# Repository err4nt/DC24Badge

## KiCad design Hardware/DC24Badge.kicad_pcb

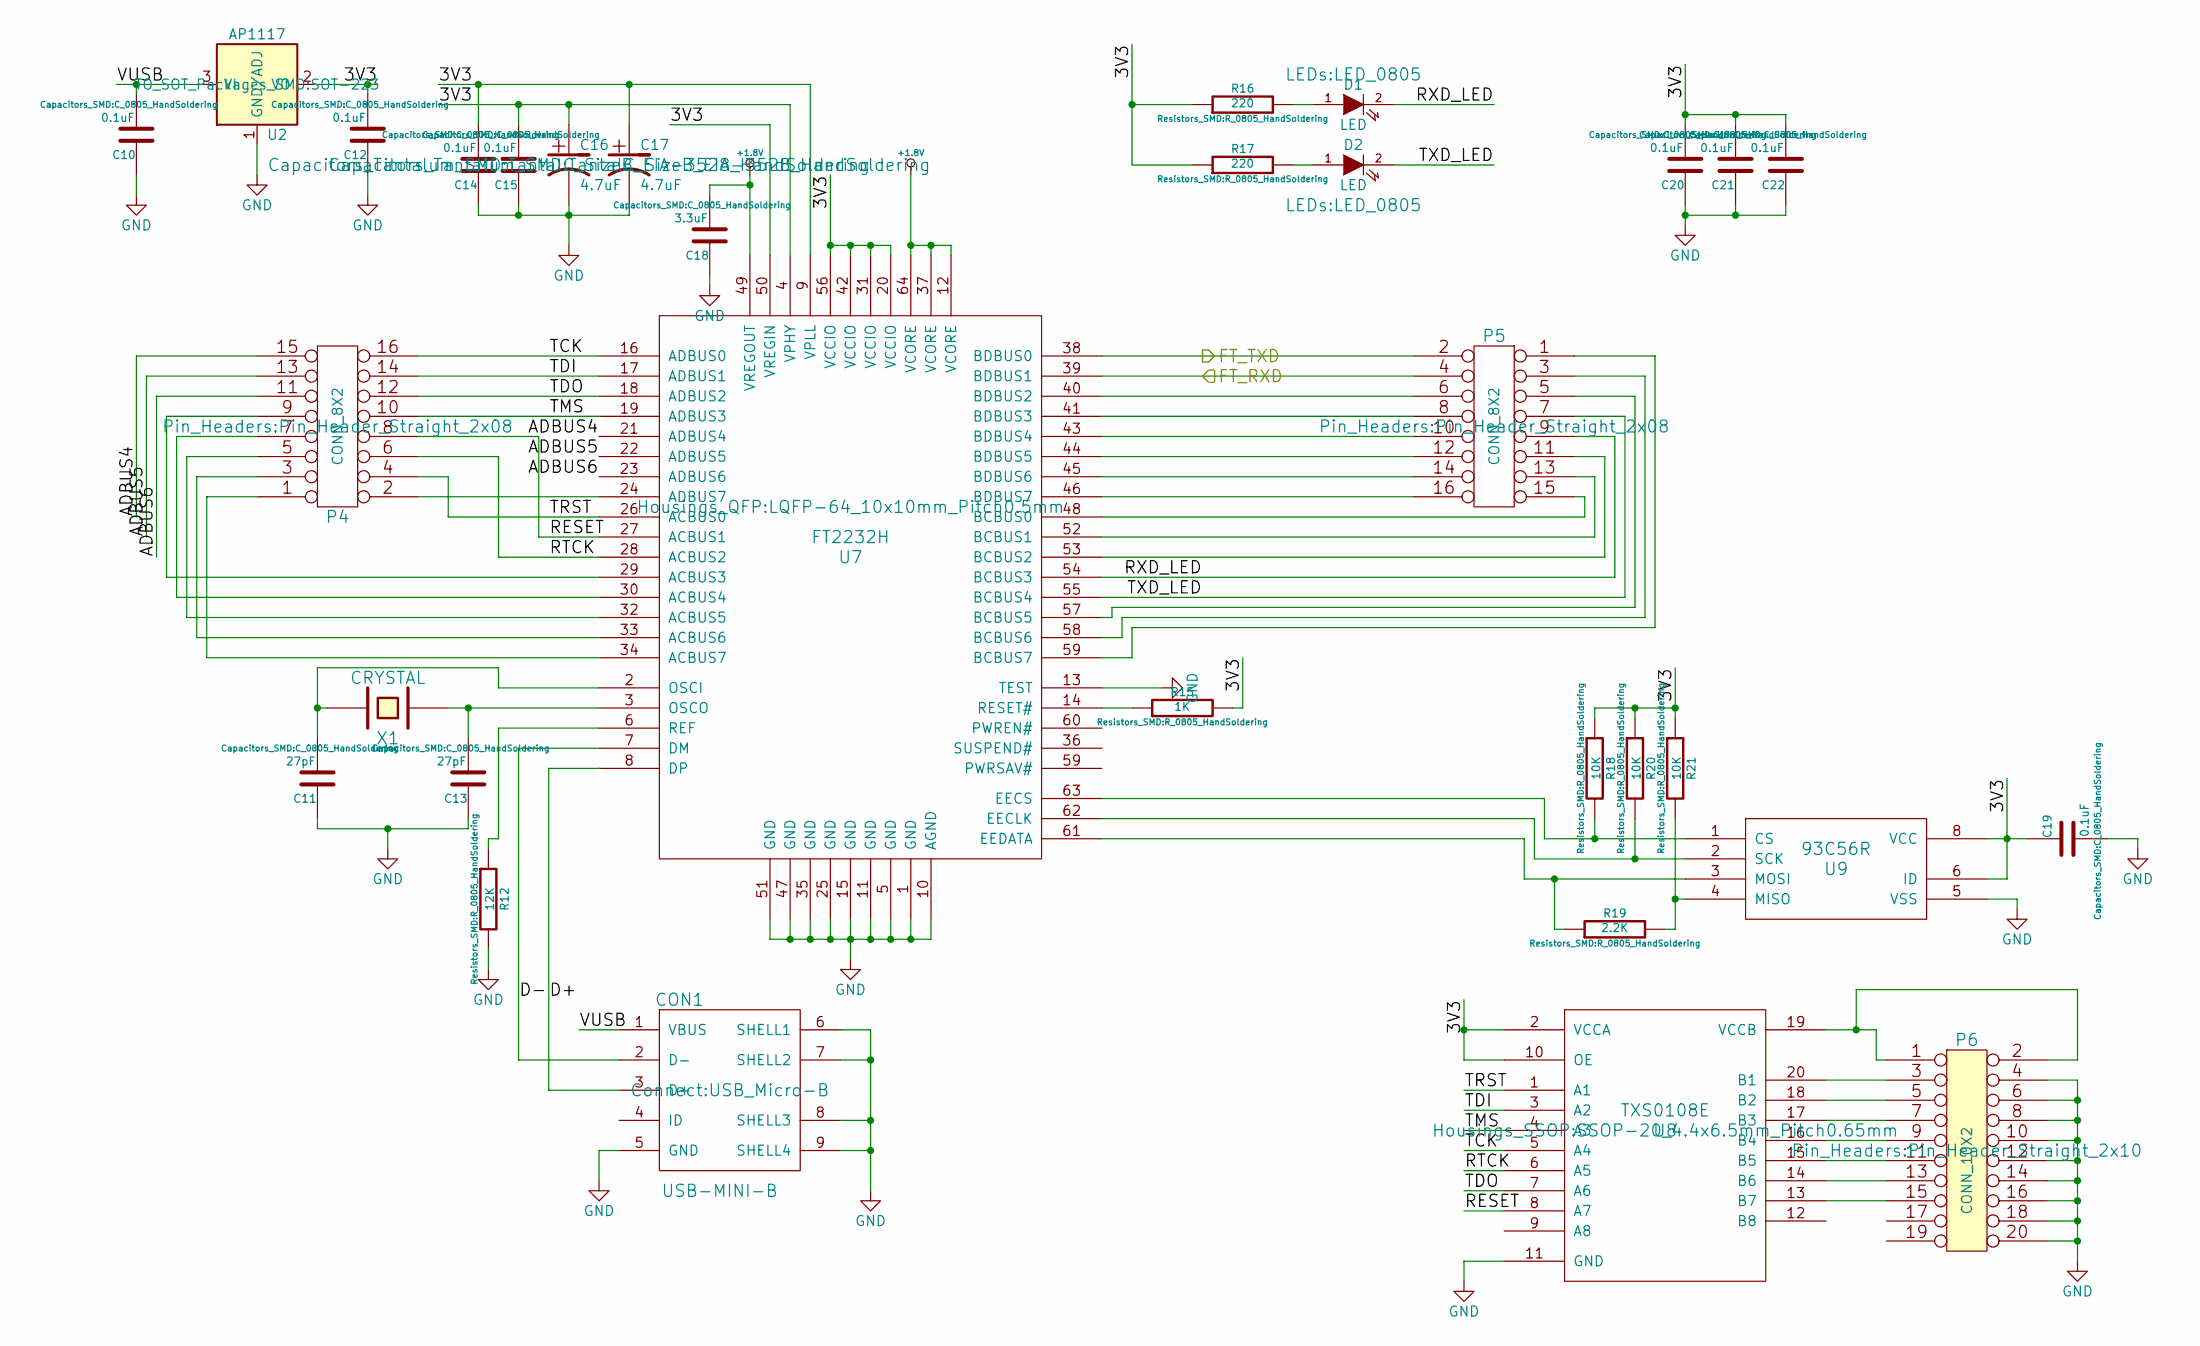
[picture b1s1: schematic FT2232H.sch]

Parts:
C10, C12, C14, C15, C19, C20, C21, C22: 0.1uF; C_0805_HandSoldering; MouserPN 710-885012207072
C11, C13: 27pF; C_0805_HandSoldering; MouserPN 80-C0805C270J5G
C16, C17: 4.7uF; TantalC_SizeB_EIA-3528_HandSoldering; MouserPN 647-F931E475MBA
C18: 3.3uF; C_0805_HandSoldering; MouserPN 77-VJ0805V335ZXQTBC
CON1: USB-MINI-B; USB_Micro-B; MouserPN 798-ZX62D-B-5PA830
D1: LED; LED_0805; MouserPN 720-LGR971-KN-1
D2: LED; LED_0805; MouserPN 720-LHR974-LP-1
P4, P5: CONN_8X2; Pin_Header_Straight_2x08
P6: CONN_10X2; Pin_Header_Straight_2x10; MouserPN 653-XG4C-2031
R12: 12K; R_0805_HandSoldering; MouserPN 667-ERJ-6GEYJ123V
R15: 1K; R_0805_HandSoldering; MouserPN 603-RC0805FR-071KL
R16, R17: 220; R_0805_HandSoldering; MouserPN 667-ERJ-6GEYJ221V
R18, R20, R21: 10K; R_0805_HandSoldering; MouserPN 588-AS08J1002ET
R19: 2.2K; R_0805_HandSoldering; MouserPN 667-ERJ-6GEYJ222V
U2: AP1117; SOT-223; MouserPN 926-LM1117MPX3.3NOPB
U7: FT2232H; LQFP-64_10x10mm_Pitch0.5mm; MouserPN 895-FT2232HL
U8: TXS0108E; SSOP-20_4.4x6.5mm_Pitch0.65mm; MouserPN 595-TXS0108EPWR
U9: 93C56R; SOIC-8_3.9x4.9mm_Pitch1.27mm; MouserPN 511-M93C56-RMN6TP
X1: CRYSTAL; HC-49V; MouserPN 520-HCA1200-SX

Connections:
+1.8V: C18.2, U7.12 (VCORE), U7.37 (VCORE), U7.49 (VREGOUT), U7.64 (VCORE)
/ESP12E/ESP_RX: P5.2, U7.38 (BDBUS0); also elsewhere on the board
/ESP12E/ESP_TX: P5.4, U7.39 (BDBUS1); also elsewhere on the board
/FT2232H/3V3: C12.2, C14.2, C15.2, C16.1, C17.1, C19.1, C20.2, C21.2, C22.2, R15.2, R16.1, R17.1, R18.1, R20.1, R21.1, U2.2 (VO), U7.4 (VPHY), U7.9 (VPLL), U7.20 (VCCIO), U7.31 (VCCIO), U7.42 (VCCIO), U7.50 (VREGIN), U7.56 (VCCIO), U8.2 (VCCA), U8.10 (OE), U9.6 (ID), U9.8 (VCC)
/FT2232H/ADBUS4: P4.15, U7.21 (ADBUS4)
/FT2232H/ADBUS5: P4.13, U7.22 (ADBUS5)
/FT2232H/ADBUS6: P4.11, U7.23 (ADBUS6)
/FT2232H/D+: CON1.3 (D+), U7.8 (DP)
/FT2232H/D-: CON1.2 (D-), U7.7 (DM)
/FT2232H/RESET: P4.8, U7.27 (ACBUS1), U8.8 (A7)
/FT2232H/RTCK: P4.6, U7.28 (ACBUS2), U8.6 (A5)
/FT2232H/RXD_LED: D1.2 (K), P5.9, U7.54 (BCBUS3)
/FT2232H/TCK: P4.16, U7.16 (ADBUS0), U8.5 (A4)
/FT2232H/TDI: P4.14, U7.17 (ADBUS1), U8.3 (A2)
/FT2232H/TDO: P4.12, U7.18 (ADBUS2), U8.7 (A6)
/FT2232H/TMS: P4.10, U7.19 (ADBUS3), U8.4 (A3)
/FT2232H/TRST: P4.4, U7.26 (ACBUS0), U8.1 (A1)
/FT2232H/TXD_LED: D2.2 (K), P5.7, U7.55 (BCBUS4)
/FT2232H/VUSB: C10.2, CON1.1 (VBUS), U2.3 (VI)
GND: C10.1, C11.1, C12.1, C13.1, C14.1, C15.1, C16.2, C17.2, C18.1, C19.2, C20.1, C21.1, C22.1, CON1.5 (GND), CON1.6 (SHELL1), CON1.7 (SHELL2), CON1.8 (SHELL3), CON1.9 (SHELL4), P6.4, P6.6, P6.8, P6.10, P6.12, P6.14, P6.16, P6.18, P6.20, R12.2, U2.1 (GND/ADJ), U7.1 (GND), U7.5 (GND), U7.10 (AGND), U7.11 (GND), U7.13 (TEST), U7.15 (GND), U7.25 (GND), U7.35 (GND), U7.47 (GND), U7.51 (GND), U8.11 (GND), U9.5 (VSS); also elsewhere on the board
unnamed: C11.2, U7.2 (OSCI), X1.2
unnamed: C13.2, U7.3 (OSCO), X1.1
unnamed: D1.1 (A), R16.2
unnamed: D2.1 (A), R17.2
unnamed: P4.1, U7.34 (ACBUS7)
unnamed: P4.2, U7.24 (ADBUS7)
unnamed: P4.3, U7.33 (ACBUS6)
unnamed: P4.5, U7.32 (ACBUS5)
unnamed: P4.7, U7.30 (ACBUS4)
unnamed: P4.9, U7.29 (ACBUS3)
unnamed: P5.3, U7.58 (BCBUS6)
unnamed: P5.5, U7.57 (BCBUS5)
unnamed: P5.6, U7.40 (BDBUS2)
unnamed: P5.8, U7.41 (BDBUS3)
unnamed: P5.10, U7.43 (BDBUS4)
unnamed: P5.11, U7.53 (BCBUS2)
unnamed: P5.12, U7.44 (BDBUS5)
unnamed: P5.13, U7.52 (BCBUS1)
unnamed: P5.14, U7.45 (BDBUS6)
unnamed: P5.15, U7.48 (BCBUS0)
unnamed: P5.16, U7.46 (BDBUS7)
unnamed: P6.1, P6.2, U8.19 (VCCB)
unnamed: P6.3, U8.20 (B1)
unnamed: P6.5, U8.18 (B2)
unnamed: P6.7, U8.17 (B3)
unnamed: P6.9, U8.16 (B4)
unnamed: P6.11, U8.15 (B5)
unnamed: P6.13, U8.14 (B6)
unnamed: P6.15, U8.13 (B7)
unnamed: R12.1, U7.6 (REF)
unnamed: R15.1, U7.14 (RESET#)
unnamed: R18.2, U7.63 (EECS), U9.1 (CS)
unnamed: R19.1, U7.61 (EEDATA), U9.3 (MOSI)
unnamed: R19.2, R21.2, U9.4 (MISO)
unnamed: R20.2, U7.62 (EECLK), U9.2 (SCK)

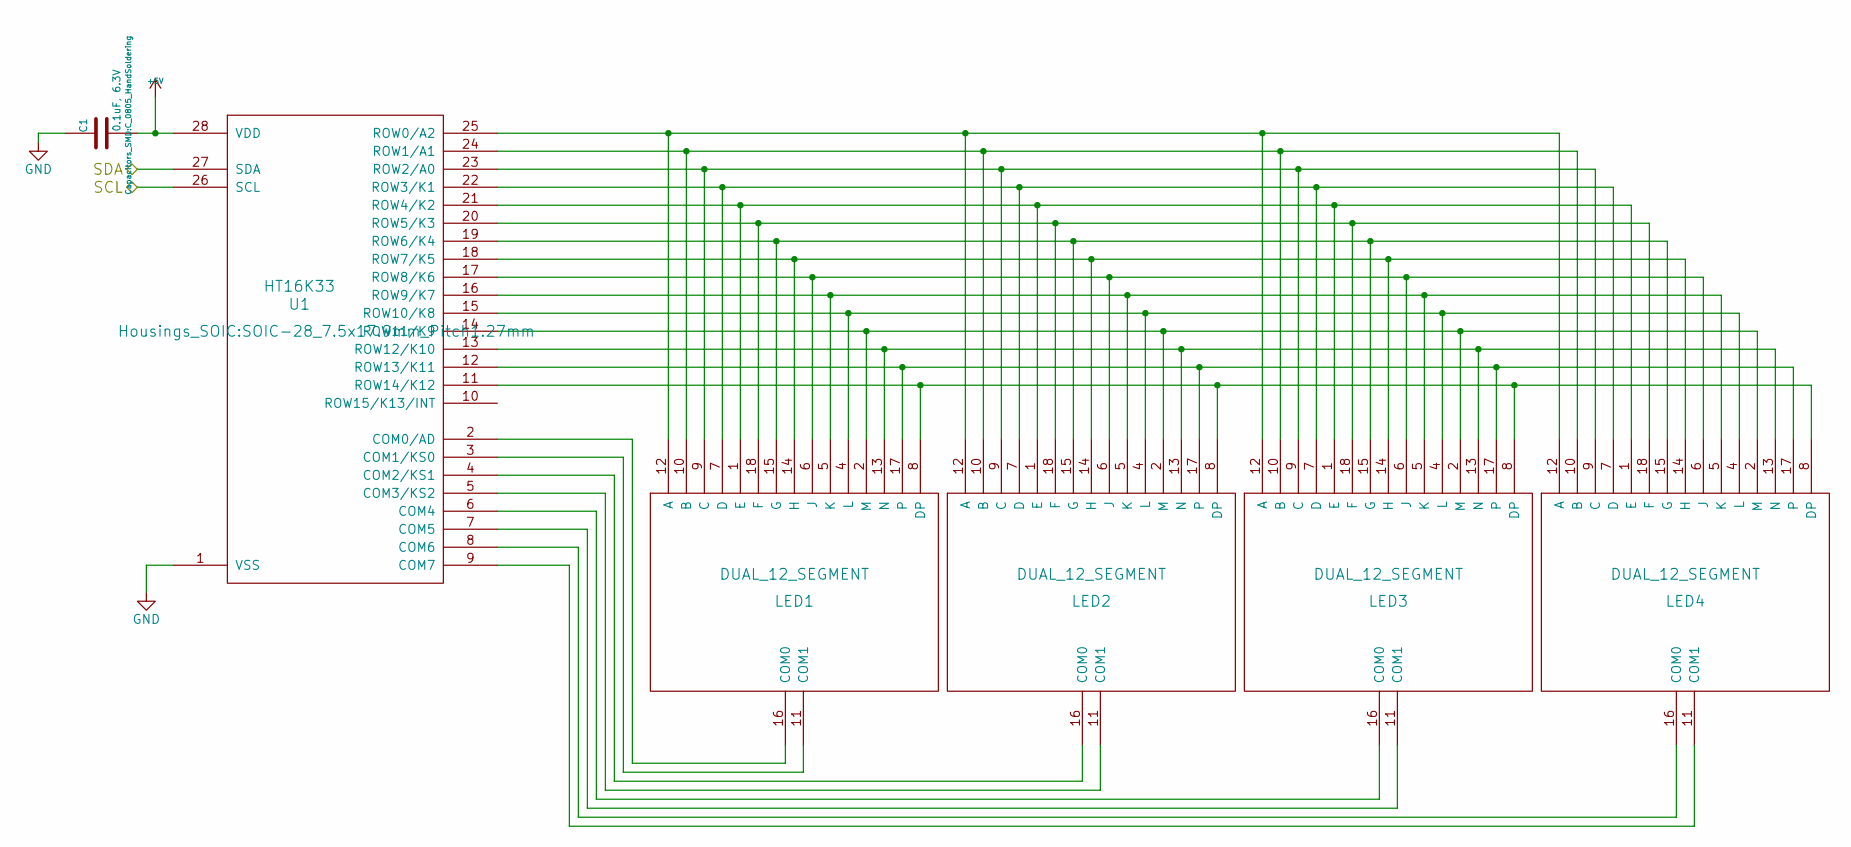
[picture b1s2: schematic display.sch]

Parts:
C1: 0.1uF, 6.3V; C_0805_HandSoldering; MouserPN 710-885012207072
LED1: DUAL_12_SEGMENT; LTP-3786E; MouserPN 859-LTP-3784E
LED2, LED3, LED4: DUAL_12_SEGMENT; LTP-3786E
U1: HT16K33; SOIC-28_7.5x17.9mm_Pitch1.27mm

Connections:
+5V: C1.2, U1.28 (VDD); also elsewhere on the board
GND: C1.1, U1.1 (VSS); also elsewhere on the board
GPIO4: U1.27 (SDA); also elsewhere on the board
GPIO5: U1.26 (SCL); also elsewhere on the board
unnamed: LED1.1 (E), LED2.1 (E), LED3.1 (E), LED4.1 (E), U1.21 (ROW4/K2)
unnamed: LED1.2 (M), LED2.2 (M), LED3.2 (M), LED4.2 (M), U1.14 (ROW11/K9)
unnamed: LED1.4 (L), LED2.4 (L), LED3.4 (L), LED4.4 (L), U1.15 (ROW10/K8)
unnamed: LED1.5 (K), LED2.5 (K), LED3.5 (K), LED4.5 (K), U1.16 (ROW9/K7)
unnamed: LED1.6 (J), LED2.6 (J), LED3.6 (J), LED4.6 (J), U1.17 (ROW8/K6)
unnamed: LED1.7 (D), LED2.7 (D), LED3.7 (D), LED4.7 (D), U1.22 (ROW3/K1)
unnamed: LED1.8 (DP), LED2.8 (DP), LED3.8 (DP), LED4.8 (DP), U1.11 (ROW14/K12)
unnamed: LED1.9 (C), LED2.9 (C), LED3.9 (C), LED4.9 (C), U1.23 (ROW2/A0)
unnamed: LED1.10 (B), LED2.10 (B), LED3.10 (B), LED4.10 (B), U1.24 (ROW1/A1)
unnamed: LED1.11 (COM1), U1.3 (COM1/KS0)
unnamed: LED1.12 (A), LED2.12 (A), LED3.12 (A), LED4.12 (A), U1.25 (ROW0/A2)
unnamed: LED1.13 (N), LED2.13 (N), LED3.13 (N), LED4.13 (N), U1.13 (ROW12/K10)
unnamed: LED1.14 (H), LED2.14 (H), LED3.14 (H), LED4.14 (H), U1.18 (ROW7/K5)
unnamed: LED1.15 (G), LED2.15 (G), LED3.15 (G), LED4.15 (G), U1.19 (ROW6/K4)
unnamed: LED1.16 (COM0), U1.2 (COM0/AD)
unnamed: LED1.17, LED2.17, LED3.17, LED4.17, U1.12 (ROW13/K11)
unnamed: LED1.18 (F), LED2.18 (F), LED3.18 (F), LED4.18 (F), U1.20 (ROW5/K3)
unnamed: LED2.11 (COM1), U1.5 (COM3/KS2)
unnamed: LED2.16 (COM0), U1.4 (COM2/KS1)
unnamed: LED3.11 (COM1), U1.7 (COM5)
unnamed: LED3.16 (COM0), U1.6 (COM4)
unnamed: LED4.11 (COM1), U1.9 (COM7)
unnamed: LED4.16 (COM0), U1.8 (COM6)

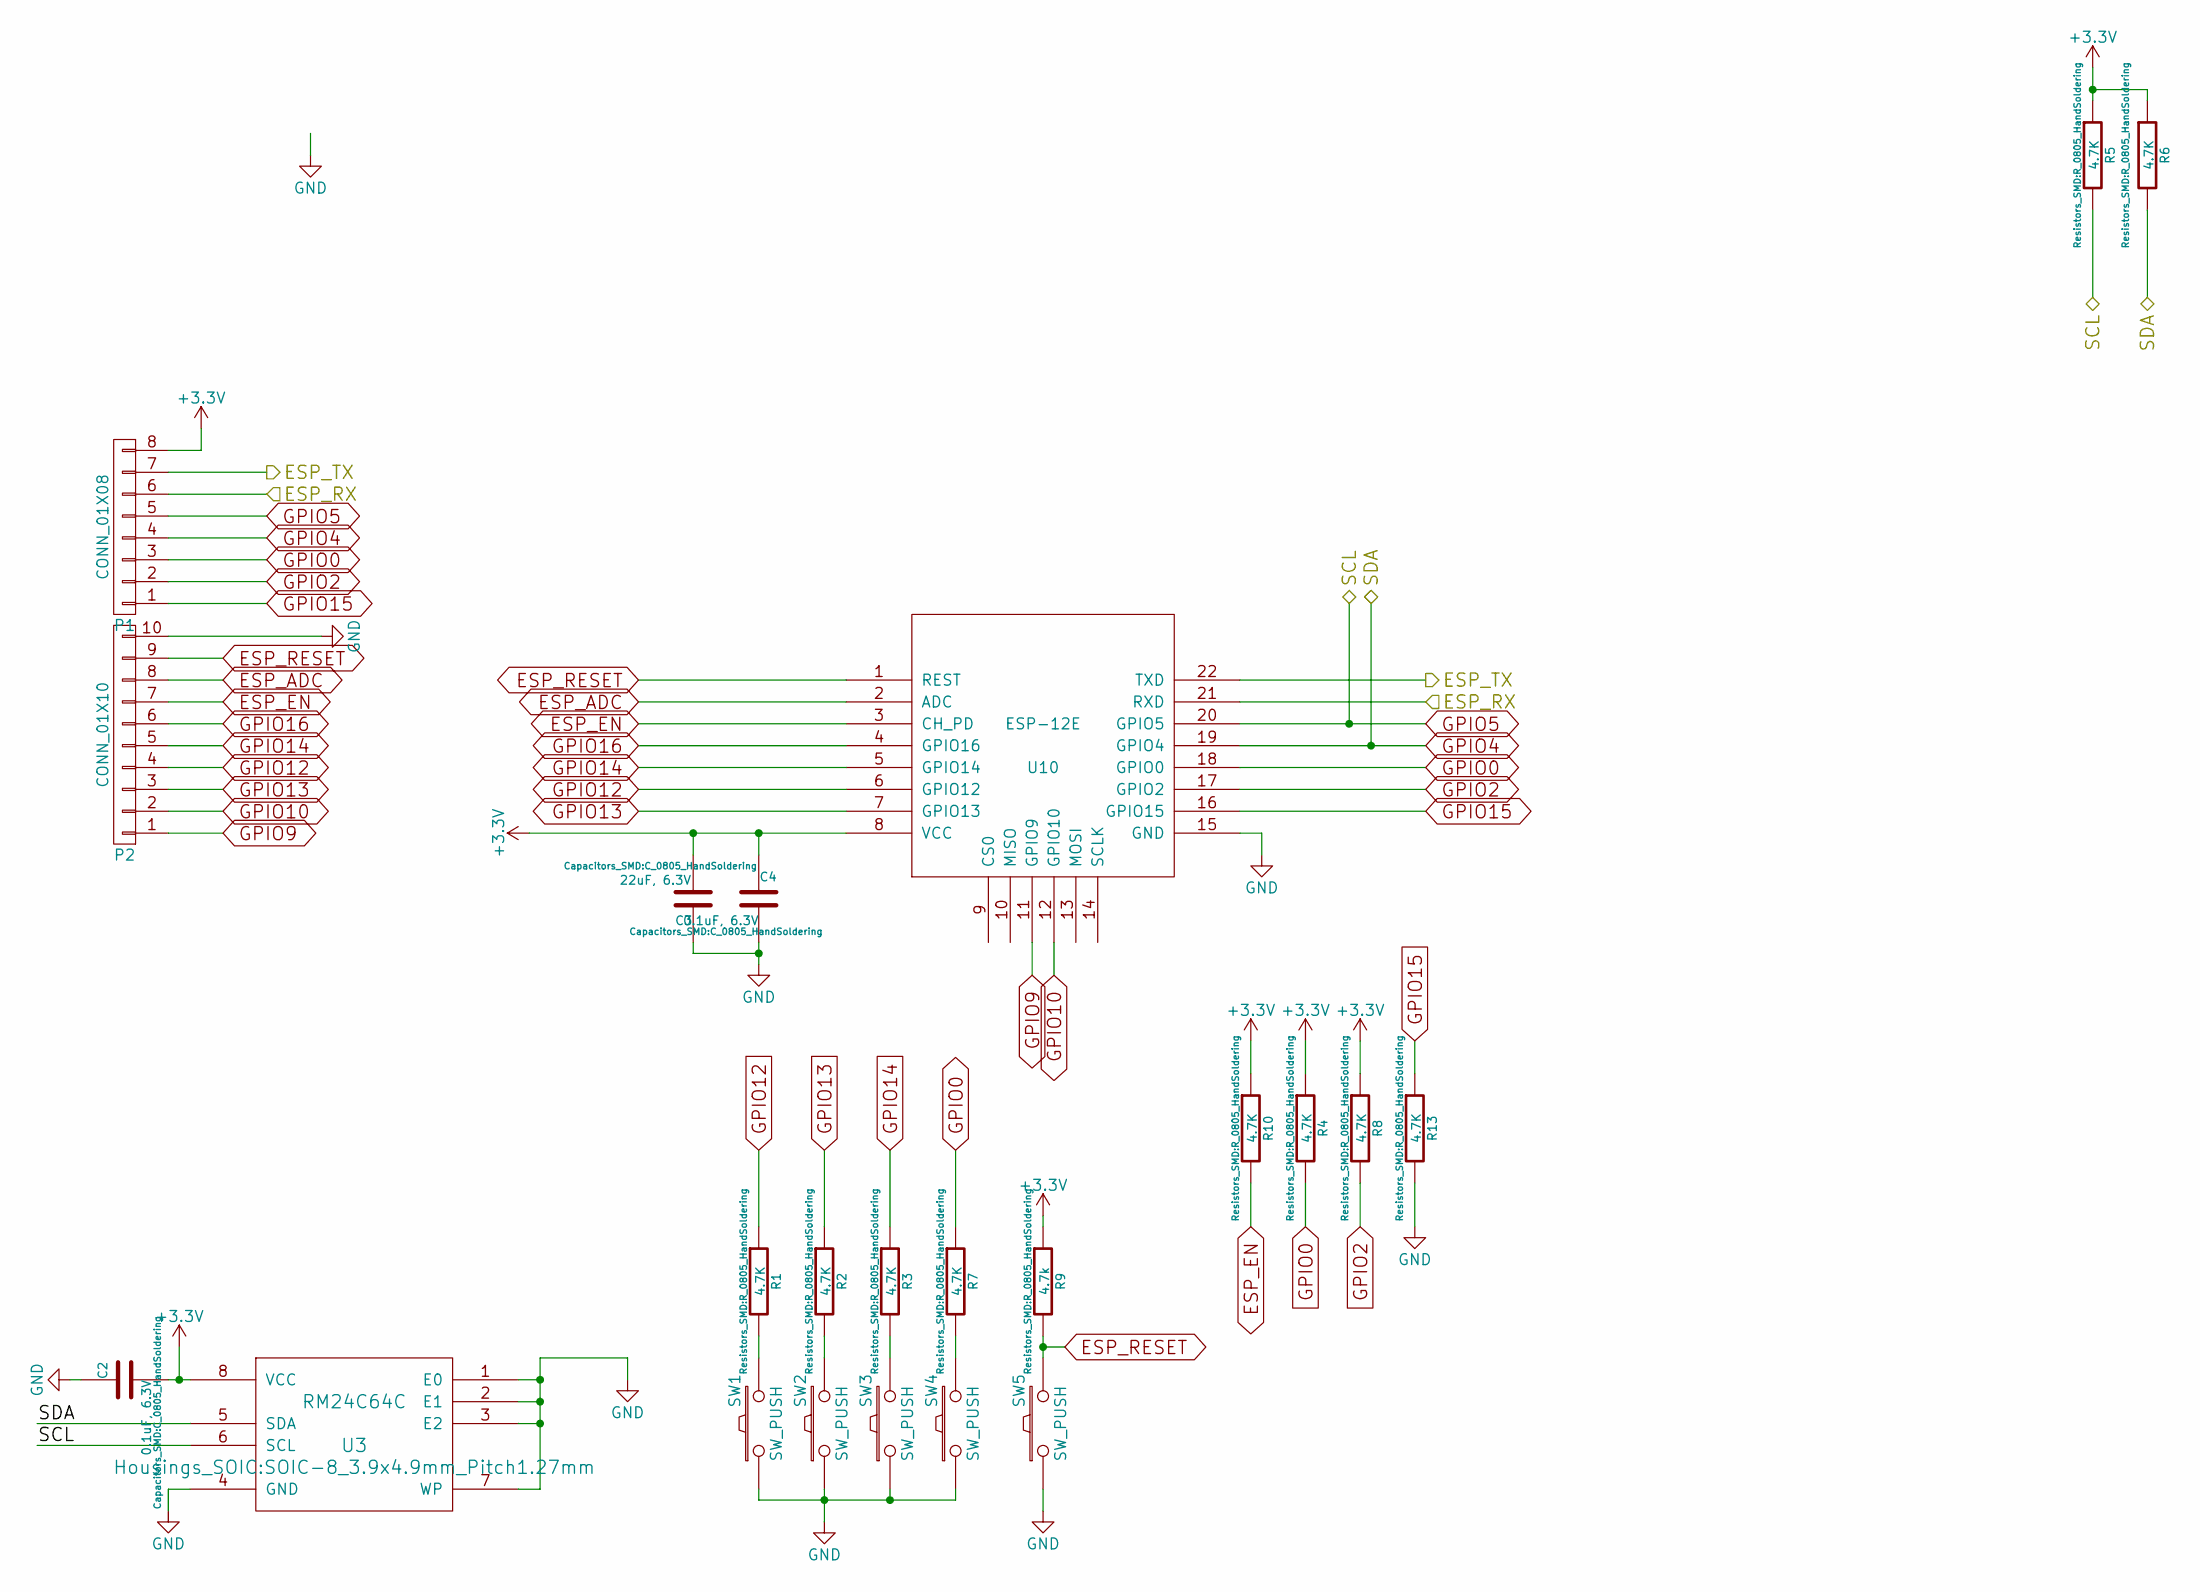
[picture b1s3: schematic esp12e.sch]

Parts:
C2, C4: 0.1uF, 6.3V; C_0805_HandSoldering; MouserPN 710-885012207072
C3: 22uF, 6.3V; C_0805_HandSoldering; MouserPN 77-VJ0805G226MXYTBC
P1: CONN_01X08; Pin_Header_Straight_1x08
P2: CONN_01X10; Pin_Header_Straight_1x10
R1, R2, R3, R5, R6, R7: 4.7K; R_0805_HandSoldering; MouserPN 667-ERJ-6GEYJ472V
R4, R8, R10, R13: 4.7K; R_0805_HandSoldering; MouserPN 588-AS08J1002ET
R9: 4.7k; R_0805_HandSoldering; MouserPN 588-AS08J1002ET
SW1, SW2, SW3, SW4, SW5: SW_PUSH; SW_SPST_EVQP0; MouserPN 667-EVQ-PLHA15
U3: RM24C64C; SOIC-8_3.9x4.9mm_Pitch1.27mm; MouserPN 988-RM24EP128A-BSNCB
U10: ESP-12E

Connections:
+3V3: C2.2, C3.2, C4.1, P1.8, R4.1, R5.1, R6.1, R8.1, R9.1, R10.1, U3.8 (VCC), U10.8 (VCC); also elsewhere on the board
/ESP12E/ESP_RX: P1.6, U10.21 (RXD); also elsewhere on the board
/ESP12E/ESP_TX: P1.7, U10.22 (TXD); also elsewhere on the board
ESP_ADC: P2.8, U10.2 (ADC)
ESP_EN: P2.7, R10.2, U10.3 (CH_PD)
ESP_RESET: P2.9, R9.2, SW5.2, U10.1 (REST)
GND: C2.1, C3.1, C4.2, P2.10, R13.2, SW1.1, SW2.1, SW3.1, SW4.1, SW5.1, U3.1 (E0), U3.2 (E1), U3.3 (E2), U3.4 (GND), U3.7 (WP), U10.15 (GND); also elsewhere on the board
GPIO0: P1.3, R4.2, R7.1, U10.18 (GPIO0)
GPIO2: P1.2, R8.2, U10.17 (GPIO2)
GPIO4: P1.4, R6.2, U3.5 (SDA), U10.19 (GPIO4); also elsewhere on the board
GPIO5: P1.5, R5.2, U3.6 (SCL), U10.20 (GPIO5); also elsewhere on the board
GPIO9: P2.1, U10.11 (GPIO9)
GPIO10: P2.2, U10.12 (GPIO10)
GPIO12: P2.4, R1.1, U10.6 (GPIO12)
GPIO13: P2.3, R2.1, U10.7 (GPIO13)
GPIO14: P2.5, R3.1, U10.5 (GPIO14)
GPIO15: P1.1, R13.1, U10.16 (GPIO15)
GPIO16: P2.6, U10.4 (GPIO16)
unnamed: R1.2, SW1.2
unnamed: R2.2, SW2.2
unnamed: R3.2, SW3.2
unnamed: R7.2, SW4.2

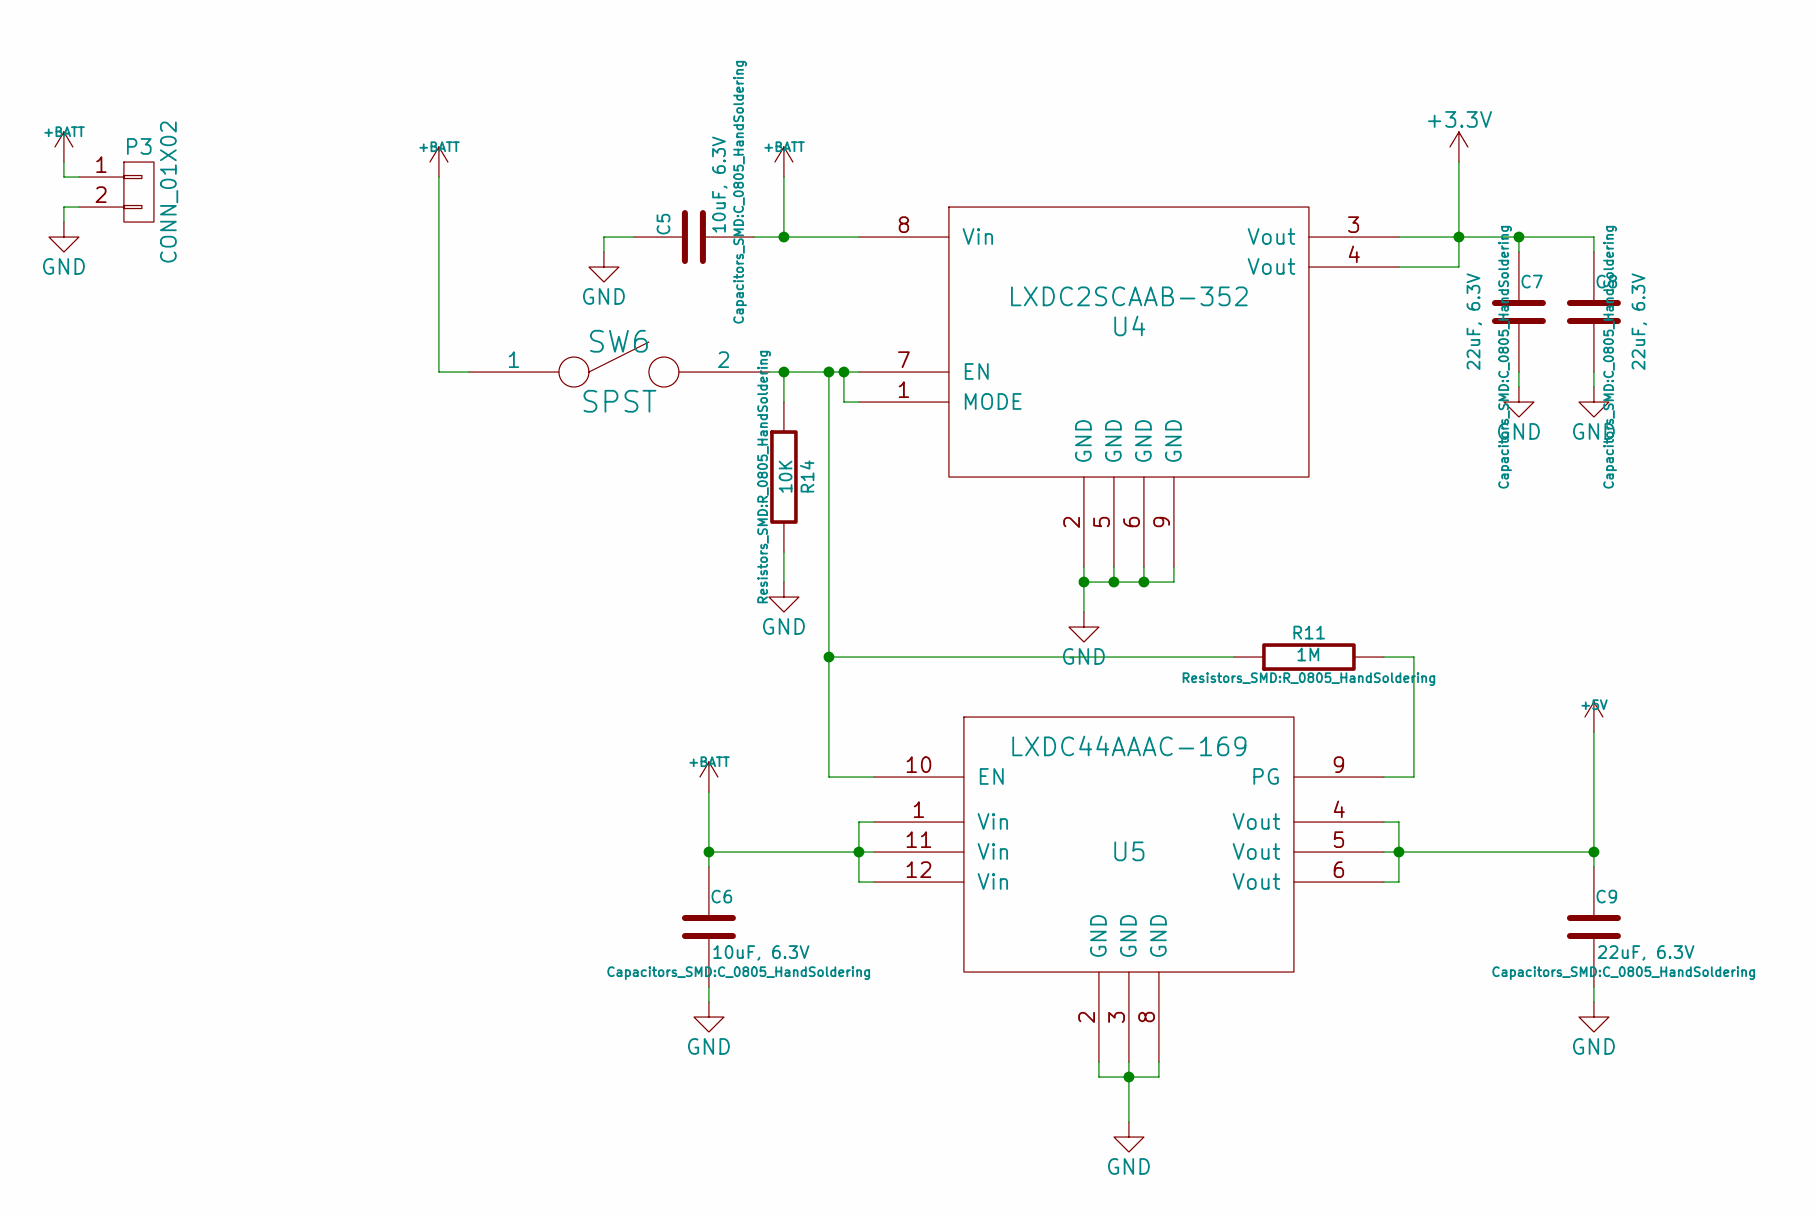
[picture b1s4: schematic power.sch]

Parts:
C5, C6: 10uF, 6.3V; C_0805_HandSoldering; MouserPN 77-VJ0805G106KXQTBC
C7, C8, C9: 22uF, 6.3V; C_0805_HandSoldering; MouserPN 77-VJ0805G226MXYTBC
P3: CONN_01X02; Pin_Header_Straight_1x02
R11: 1M; R_0805_HandSoldering; MouserPN 603-RT0805FRD071ML
R14: 10K; R_0805_HandSoldering; MouserPN 603-RT0805FRD071ML
SW6: SPST; MS-100406; MouserPN 10TC605
U4: LXDC2SCAAB-352; MouserPN 81-LXDC2SCAAB-352
U5: LXDC44AAAC-169; LXDC44A; MouserPN 81-LXDC44AAAC-169

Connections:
+3V3: C7.1, C8.1, U4.3 (Vout), U4.4 (Vout); also elsewhere on the board
+5V: C9.1, U5.4 (Vout), U5.5 (Vout), U5.6 (Vout); also elsewhere on the board
+BATT: C5.2, C6.1, P3.1, SW6.1, U4.8 (Vin), U5.1 (Vin), U5.11 (Vin), U5.12 (Vin)
GND: C5.1, C6.2, C7.2, C8.2, C9.2, P3.2, R14.2, U4.2 (GND), U4.5 (GND), U4.6 (GND), U4.9 (GND), U5.2 (GND), U5.3 (GND), U5.8 (GND); also elsewhere on the board
unnamed: R11.1, R14.1, SW6.2, U4.1 (MODE), U4.7 (EN), U5.10 (EN)
unnamed: R11.2, U5.9 (PG)

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
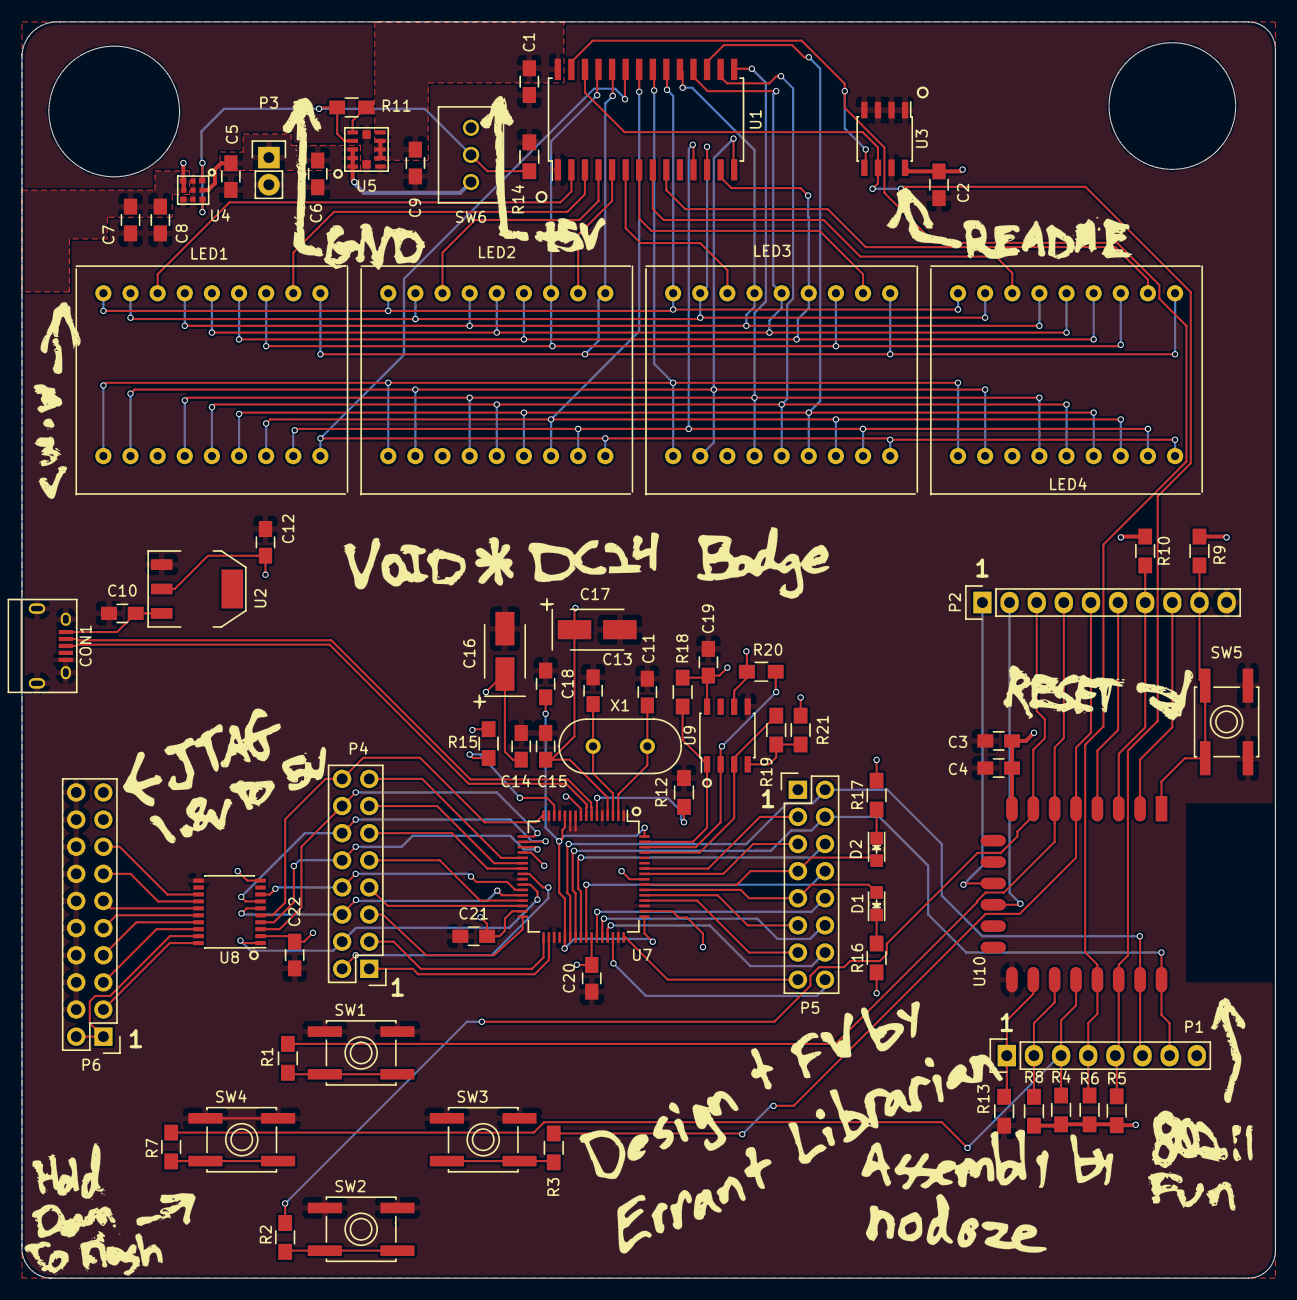
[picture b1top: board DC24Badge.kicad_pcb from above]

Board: 2 copper layers, 117.4 x 117.6 mm, 72 parts (0 on the bottom side), 101 nets.

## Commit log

2016-07-28 Uhh... huh. Thought I was more out of date than I was...
2016-07-28 Blingy display function 1 done
2016-07-28 Nick add menu partly done
2016-07-29 Text entry
2016-07-29 Instruction text
2016-07-30 Gets through the inital setup now
2016-07-30 Scroll working
2016-07-30 Menu system working
2016-07-30 Fixed bug where menu could not be entered. Badge wipe works. Setup sequence working.
2016-07-30 Add delay after sneakers, fix random selection
2016-07-31 Random text selection, fix . in font
2016-07-31 Add menu item to change nick
2016-07-31 Badge greet function working, fixed scroll issue
2016-08-01 End of day
2016-08-02 Mostly done
2016-08-06 No plan survives contact with the enemy
